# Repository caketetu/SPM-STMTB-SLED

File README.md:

# SPM-STMTB-SLED

## 概要

SPM-STMTBを使用したフルカラーLED御ボード。LEDポートは4ch実装した。
SK6812フルカラーLEDにて動作を確認

## 機能

* 4chのフルカラーLED制御信号を出力
* 1chあたり最大32LEDの接続
* バッファ書き込みモード
* 全LED同時制御モード
* 三種類のサンプルモード
* RS485,CANインターフェース
* Enable信号入力によるLED制御の上書き

## ピンアサイン
| Function       | Pin  | 備考 |
| -------------- | ---- | ---- |
| TIM1_CH1       | PA0  |   LED_OUT1   |
| TIM1_CH2       | PA1  |   LED_OUT2   |
| USART2_TX      | PA2  |   SYS-RS485   |
| TIM1_CH4     | PA3  |   LED_OUT4   |
| GPIO_Input     | PA4  |      |
| SPI1_SCK       | PA5  |   SYS-SPI   |
| SPI1_MISO      | PA6  |   SYS-SPI   |
| SPI1_MOSI      | PA7  |   SYS-SPI   |
| TIM1_CH1       | PA8  |      |
| USART1_TX      | PA9  |  SYS-UART    |
| USART1_RX      | PA10 |  SYS-UART    |
| FDCAN1_RX      | PA11 |  SYS-CANFD    |
| FDCAN1_TX      | PA12 |  SYS-CANFD    |
| DEBUG_SWDIO    | PA13 |  SYS-DEBUG    |
| DEBUG_SWCLK    | PA14 |  SYS-DEBUG    |
| USART2_RX      | PA15 |  SYS-RS485    |
| SPI1_NSS       | PB0  |  SYS-SPI    |
| GPIO_Output    | PB1  |      |
| GPIO_Output    | PB2  |     |
| GPIO_Output    | PB3  |      |
| GPIO_Output    | PB4  |  SYS-LED1    |
| GPIO_Input     | PB5  |  SYS-EN    |
| TIM1_CH3    | PB6  |  LED_OUT3    |
| GPIO_Output    | PB7  |      |
| GPIO_Output    | PB8  |      |
| GPIO_Input     | PB9  |      |
| GPIO_Output    | PC6  |   SYS-LED0    |
| RCC_OSCIN      | PC14 |   SYS-CLOCK   |
| RCC_OSCOUT     | PC15 |   SYS-CLOCK   |
| RCC_MCO        | PF2  |   SYS-DEBUG   |

※SYS-はSPM共通インターフェース

## 開発環境

| 項目       | 内容                      |
| -------- | ----------------------- |
| MCU      | STM32C092KBT6           |
| IDE      | STM32CubeIDE for VSCode |
| CubeMX   | STM32CubeMX 6.15.0      |
| Firmware | STM32CubeC0             |
| Language | C                       |

## 実装予定機能

* [ ] 4chぶんのバッファ制御

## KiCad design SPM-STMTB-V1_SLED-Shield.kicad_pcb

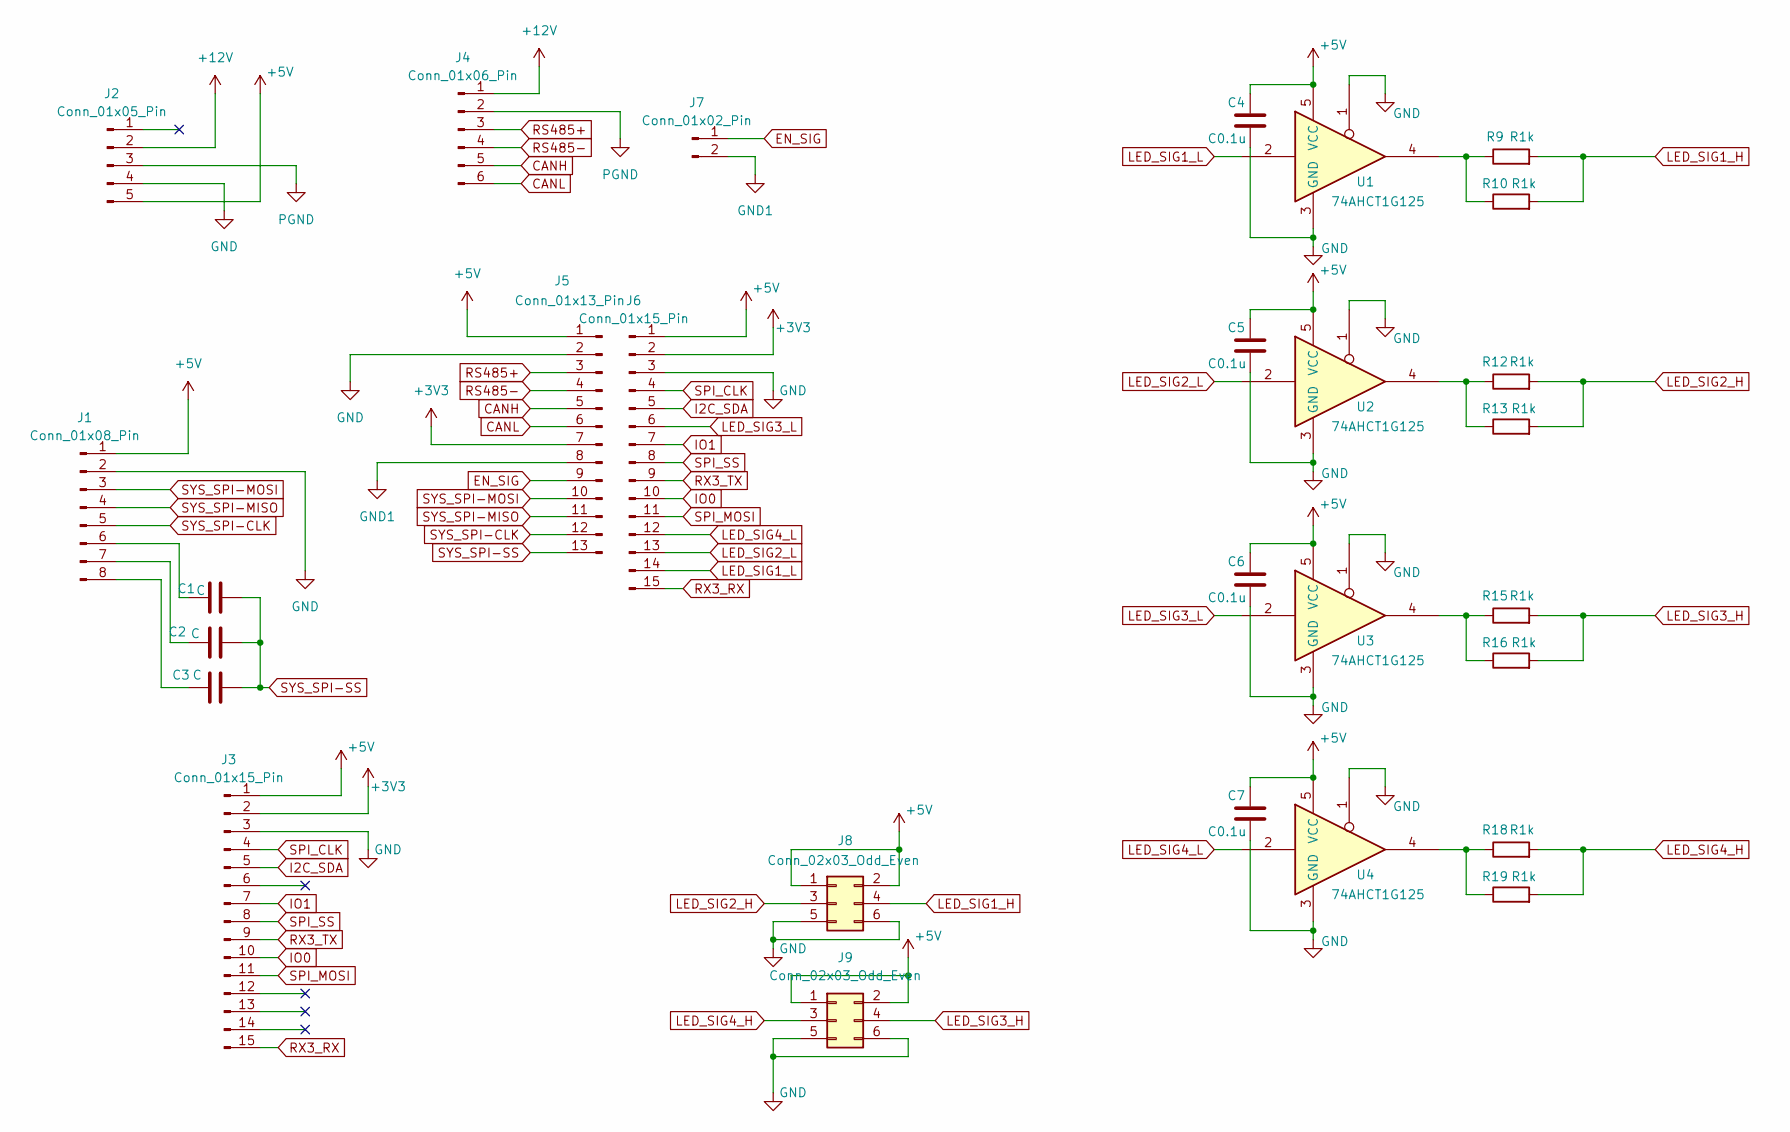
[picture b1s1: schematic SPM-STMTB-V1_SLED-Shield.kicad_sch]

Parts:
C1, C2, C3: C; C_0402_1005Metric_Pad0.74x0.62mm_HandSolder
C4, C5, C6, C7: C0.1u; C_0603_1608Metric_Pad1.08x0.95mm_HandSolder
J1: Conn_01x08_Pin; PinSocket_1x08_P2.54mm_Vertical
J2: Conn_01x05_Pin; PinSocket_1x05_P2.54mm_Vertical
J3, J6: Conn_01x15_Pin; PinSocket_1x15_P2.54mm_Vertical
J4: Conn_01x06_Pin; PinHeader_1x06_P2.54mm_Vertical
J5: Conn_01x13_Pin; PinSocket_1x13_P2.54mm_Vertical
J7: Conn_01x02_Pin; PinSocket_1x02_P2.54mm_Vertical
J8, J9: Conn_02x03_Odd_Even; PinHeader_2x03_P2.54mm_Horizontal
R9, R10, R12, R13, R15, R16, R18, R19: R1k; R_0603_1608Metric_Pad0.98x0.95mm_HandSolder
U1, U2, U3, U4: 74AHCT1G125; SOT-23-5_HandSoldering

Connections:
+3V3: J3.2, J5.7, J6.2
+5V: C4.1, C5.1, C6.1, C7.1, J1.1, J2.5, J3.1, J5.1, J6.1, J8.1, J8.2, J9.1, J9.2, U1.5 (VCC), U2.5 (VCC), U3.5 (VCC), U4.5 (VCC)
+12V: J2.2, J4.1
CANH: J4.5, J5.5
CANL: J4.6, J5.6
EN_SIG: J5.9, J7.1
GND: C4.2, C5.2, C6.2, C7.2, J1.2, J2.4, J3.3, J5.2, J6.3, J8.5, J8.6, J9.5, J9.6, U1.1, U1.3 (GND), U2.1, U2.3 (GND), U3.1, U3.3 (GND), U4.1, U4.3 (GND)
GND1: J5.8, J7.2
I2C_SDA: J3.5, J6.5
IO0: J3.10, J6.10
IO1: J3.7, J6.7
LED_SIG1_H: J8.4, R9.2, R10.2
LED_SIG1_L: J6.14, U1.2
LED_SIG2_H: J8.3, R12.2, R13.2
LED_SIG2_L: J6.13, U2.2
LED_SIG3_H: J9.4, R15.2, R16.2
LED_SIG3_L: J6.6, U3.2
LED_SIG4_H: J9.3, R18.2, R19.2
LED_SIG4_L: J6.12, U4.2
unnamed: C1.1, J1.6
unnamed: C2.1, J1.7
unnamed: C3.1, J1.8
unnamed: R9.1, R10.1, U1.4
unnamed: R12.1, R13.1, U2.4
unnamed: R15.1, R16.1, U3.4
unnamed: R18.1, R19.1, U4.4
PGND: J2.3, J4.2
RS485+: J4.3, J5.3
RS485-: J4.4, J5.4
RX3_RX: J3.15, J6.15
RX3_TX: J3.9, J6.9
SPI_CLK: J3.4, J6.4
SPI_MOSI: J3.11, J6.11
SPI_SS: J3.8, J6.8
SYS_SPI-CLK: J1.5, J5.12
SYS_SPI-MISO: J1.4, J5.11
SYS_SPI-MOSI: J1.3, J5.10
SYS_SPI-SS: C1.2, C2.2, C3.2, J5.13

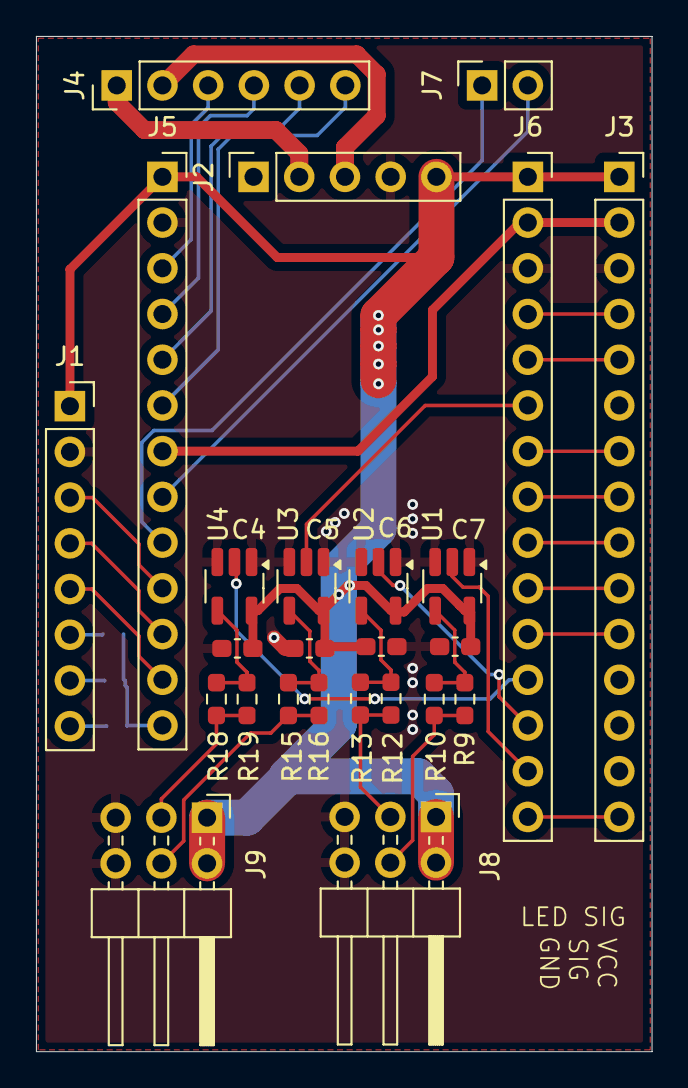
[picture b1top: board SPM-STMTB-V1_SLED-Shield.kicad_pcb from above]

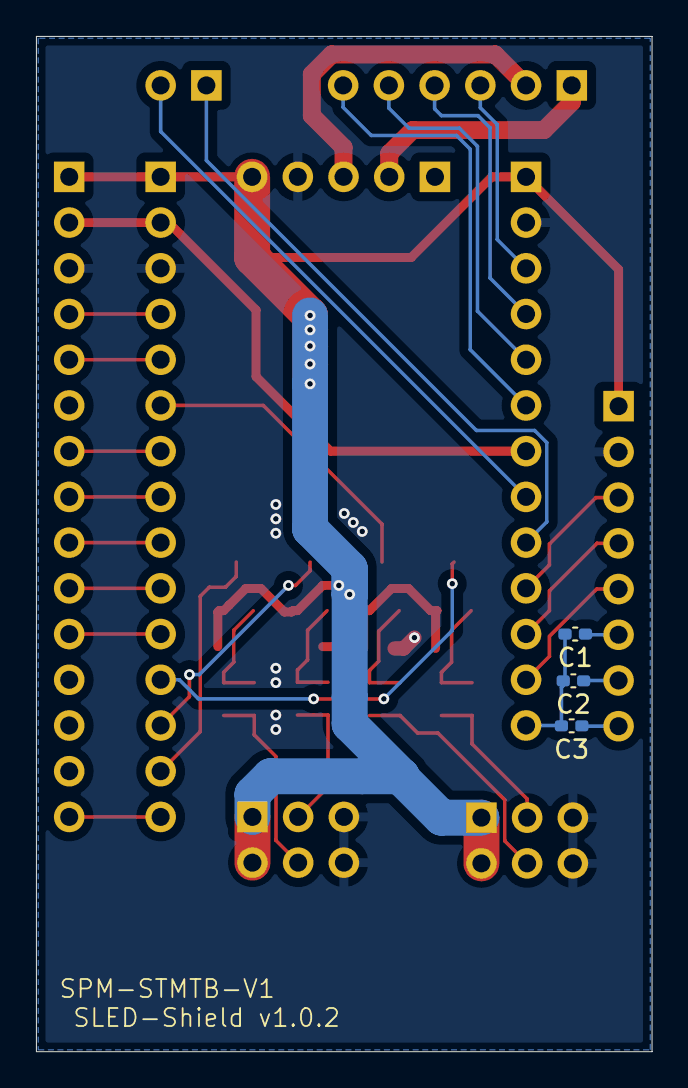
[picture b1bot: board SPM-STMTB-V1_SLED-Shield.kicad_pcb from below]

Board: 2 copper layers, 34.2 x 56.4 mm, 28 parts (3 on the bottom side), 38 nets.
